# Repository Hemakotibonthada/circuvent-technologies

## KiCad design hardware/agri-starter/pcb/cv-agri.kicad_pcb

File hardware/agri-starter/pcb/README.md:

# Agri Starter PCB - KiCad project + fab checklist

Design source: SCHEMATIC.md (netlist) + BOM.csv. Open cv-agri.kicad_pro in KiCad 8, capture, lay out, export.

## Board spec
- 2-layer FR4, 1.6 mm, HASL lead-free, 2 oz copper on mains.
- >= 8 mm creepage / 6 mm clearance mains-to-LV; isolate each phase-sense input.
- Size target ~ 80 x 60 mm; 4x M3.
- 4 V buck + 1000u bulk at the SIM800L; conformal-coat + IP54 glands for the field.

## Pre-fab (DFM) checklist
- [ ] ERC/DRC clean at fab rules; mains clearances as keepout
- [ ] Contactor-coil relay + flyback verified; phase-sense optos isolated
- [ ] SIM800L on its own 4V buck + bulk cap
- [ ] Test points: 5V, 3V3, GND, IO26/34, UART2
- [ ] UART/EN/IO0 pads for the flashing jig; fiducials

## Export for fab / assembly
- [ ] Gerbers + Excellon -> gerbers/; IPC-356 netlist
- [ ] BOM (BOM.csv) + CPL/centroid; PDF assembly + 3D STEP
- [ ] Order boards + stencil

## Bring-up (EVT)
- [ ] Rails before ESP32; flash test firmware over jig
- [ ] Relay drives a test contactor; mains-sense reads phase HIGH/LOW
- [ ] SIM registers; a missed call toggles the pump
- [ ] Dry-run: pump won't start with sense LOW; auto-restarts on return

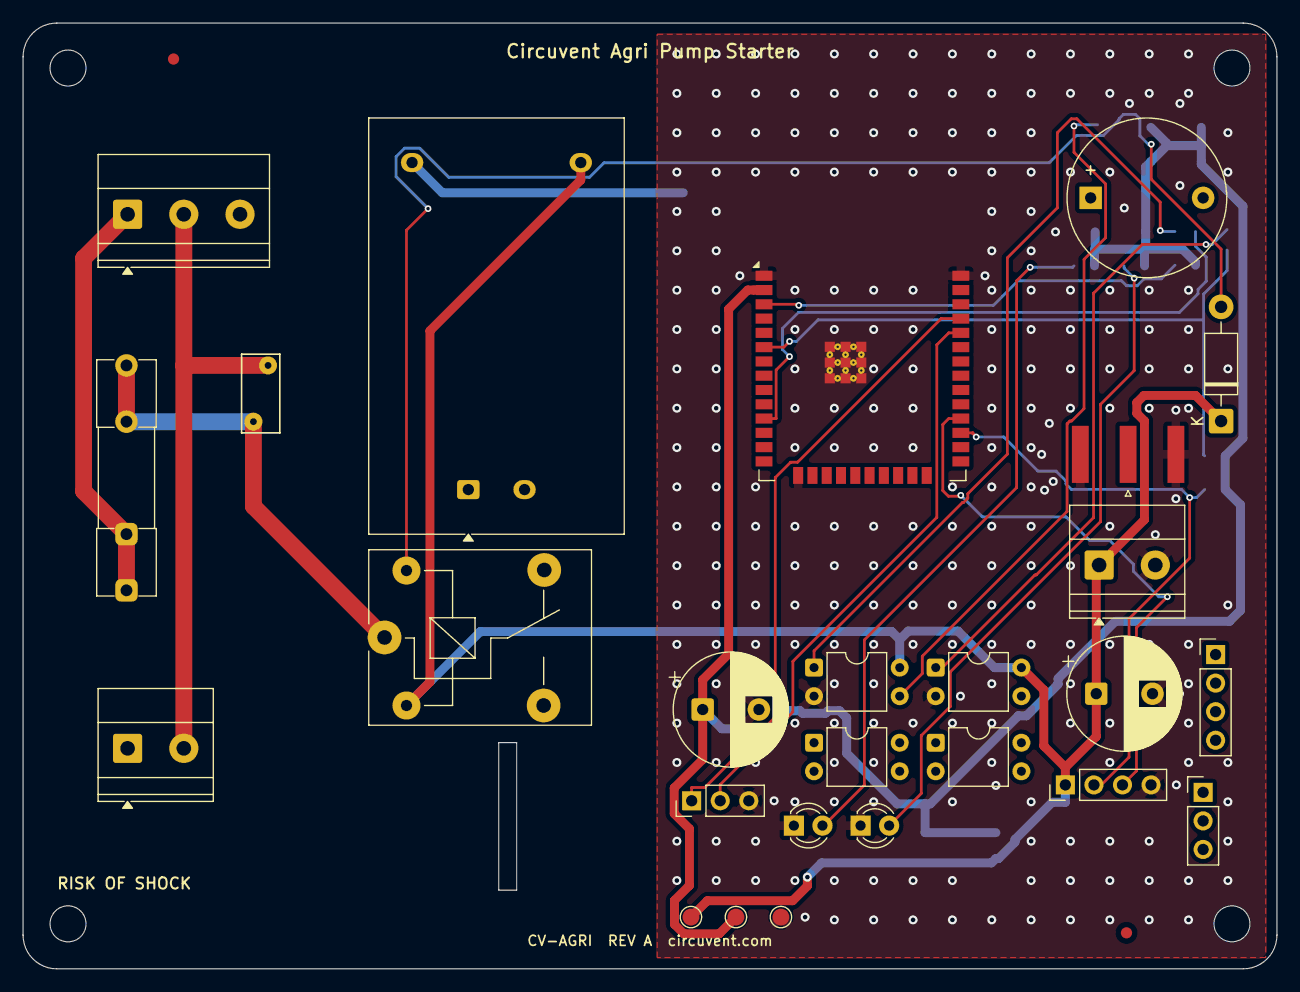
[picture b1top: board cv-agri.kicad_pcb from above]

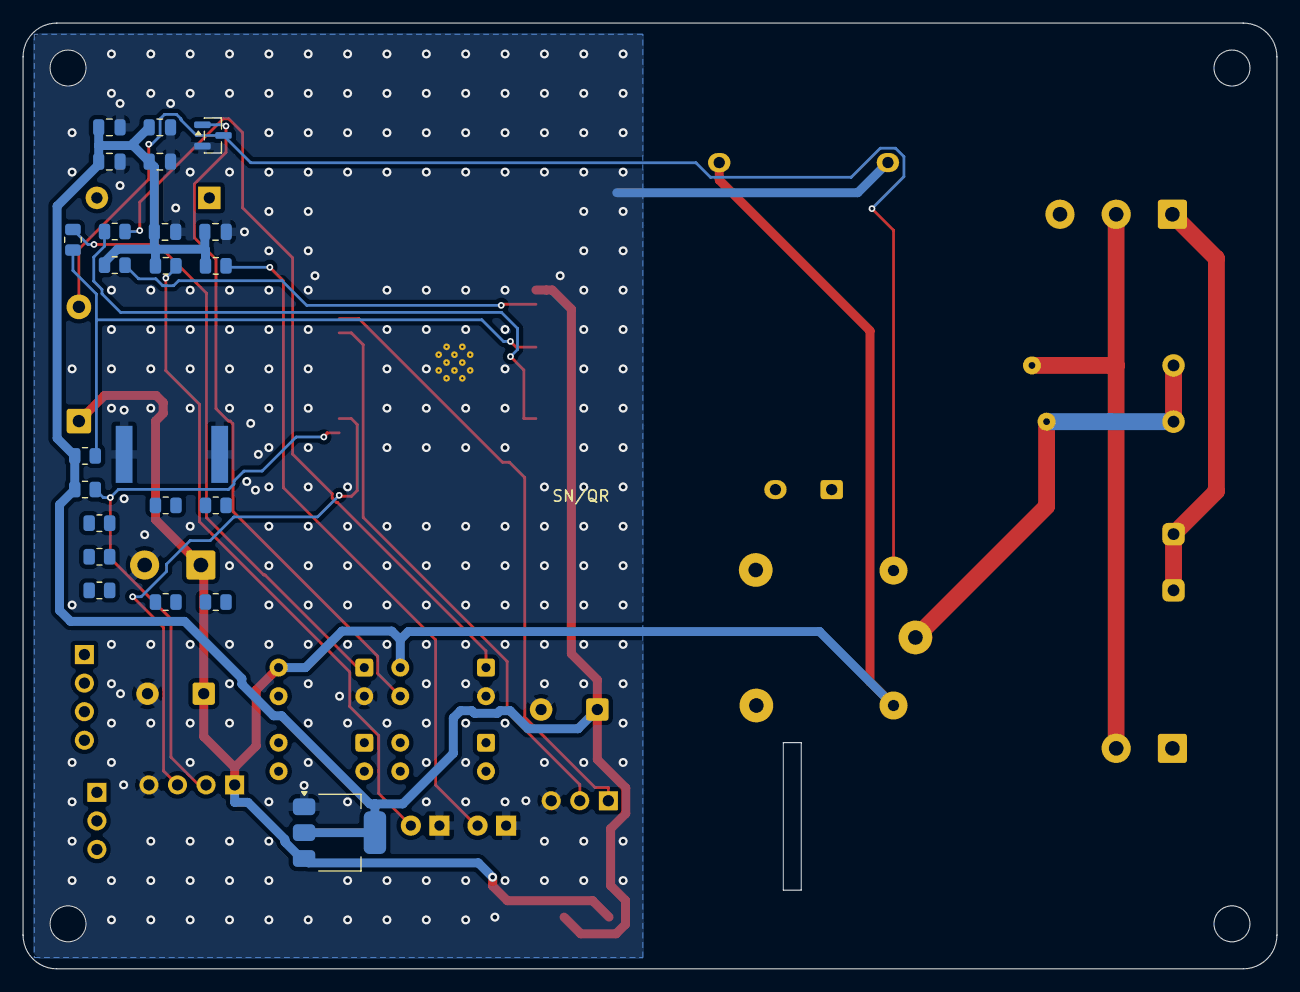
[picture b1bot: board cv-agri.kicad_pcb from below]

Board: 2 copper layers, 111.5 x 84.1 mm, 54 parts (22 on the bottom side), 20 nets.

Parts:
ANT1: GSM antenna (SMA/IPEX); SMA_Amphenol_132289_EdgeMount
C1: 470uF/10V; CP_Radial_D10.0mm_P5.00mm
C2, C3, C4, C5, C6, C7: 100nF/100uF; C_0805_2012Metric
Cs: 1000uF/6.3V; CP_Radial_D10.0mm_P5.00mm
D1: 1N4007; D_DO-41_SOD81_P10.16mm_Horizontal
F1: 1A slow-blow; Fuseholder_Clip-5x20mm_Littelfuse_111_Inline_P20.00x5.00mm_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
FB1: Buzzer 5V; Buzzer_D14mm_H7mm_P10mm
FID1, FID2: Fiducial; Fiducial_1mm_Mask2mm
J1: 2P 5.08mm; TerminalBlock_Phoenix_MKDS-1,5-3_1x03_P5.00mm_Horizontal
J2: 2P 5.08mm; TerminalBlock_Phoenix_MKDS-1,5-2_1x02_P5.00mm_Horizontal
J3: 4P 5.08mm; TerminalBlock_Phoenix_MKDS-1,5-2_1x02_P5.00mm_Horizontal
JP: 3P 2.54mm; PinHeader_1x03_P2.54mm_Vertical
K1: SRD-05VDC-SL-C; Relay_SPDT_SANYOU_SRD_Series_Form_C
LED0, LED1: 3mm; LED_D3.0mm
M1: SIM800L; PinHeader_1x04_P2.54mm_Vertical
MH1, MH2, MH3, MH4: MountingHole; MountingHole_3.2mm_M3
PC1: PC817; DIP-4_W7.62mm
PC2, PC3, PC4: PC814 (AC input); DIP-4_W7.62mm
PS1: HLK-PM01 (5V 3W); Converter_ACDC_Hi-Link_HLK-PMxx
Q1: S8050; SOT-23
R1, R2, R3, R4, R5, R6, R7, R8, R9, R10, R11, R12, R13, R14: 10k/1k/330 + opto R; R_0805_2012Metric
RV1: 7D471K; RV_Disc_D7mm_W3.4mm_P5mm
SIM1: Micro-SIM holder; PinHeader_1x03_P2.54mm_Vertical
TP1: +5V; TestPoint_Pad_D1.5mm
TP2: +3V3; TestPoint_Pad_D1.5mm
TP3: GND; TestPoint_Pad_D1.5mm
U1: ESP32-WROOM-32E (4MB); ESP32-WROOM-32E
U2: AMS1117-3.3; SOT-223-3_TabPin2
U3: MP1584 buck (4V); PinHeader_1x04_P2.54mm_Vertical

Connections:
+3V3: C2.1, C3.1, C4.1, C5.1, C6.1, C7.1, Cs.1, R3.1, R4.1, R5.1, R6.1, R7.1, TP2.1, U1.2, U2.2
+5V: C1.1, D1.1, J3.1, K1.2, M1.1, PC1.4, PC2.4, PS1.4, TP1.1, U2.3
AC_L: F1.1, J1.1
AC_L_FUSED: F1.2, K1.1, PS1.1, RV1.1
AC_N: J1.2, J2.2, PS1.2, RV1.2
EN: R3.2, U1.3
GND: ANT1.2, C1.2, C2.2, C3.2, C4.2, C5.2, C6.2, C7.2, Cs.2, J3.2, JP.3, LED0.1, LED1.1, M1.4, PC1.2, PC2.2, PS1.3, Q1.2, TP3.1, U1.1, U1.15, U1.38, U1.39, U2.1
LED0_A: LED0.2, R4.2
LED1_A: LED1.2, R5.2
MAINS_SENSE: R2.1, R6.2, U1.6
MAINS_SENSE_OPT: PC2.1, R2.2
PUMP_RELAY: R1.1, U1.11
PUMP_RELAY_COIL: D1.2, K1.5, Q1.3
PUMP_RELAY_DRV: PC1.3, Q1.1
PUMP_RELAY_OPT: PC1.1, R1.2
PUMP_RELAY_SW: J2.1, K1.3
SIM_RX: M1.2, R7.2, U1.27
SIM_TX: M1.3, U1.28
UART_RX: JP.2, U1.34
UART_TX: JP.1, U1.35

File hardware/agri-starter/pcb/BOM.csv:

Ref,Qty,Value/Part,Package,Description,Notes
U1,1,ESP32-WROOM-32E (4MB),SMD module,Wi-Fi/BLE MCU module,Main controller
PS1,1,HLK-PM01 (5V 3W),SIP,230VAC -> 5VDC isolated PSU,From one phase
U2,1,AMS1117-3.3,SOT-223,5V -> 3.3V LDO,MCU rail
U3,1,MP1584 buck (4V),module/SMD,5V -> ~4V for SIM800L,2 A capable
M1,1,SIM800L,module,2G GSM (missed call + SMS),
PC1,1,PC817,DIP-4,Opto-isolator,Relay drive
PC2-PC4,3,PC814 (AC input),DIP-4,Phase-present optos,Up to 3 phases
Q1,1,S8050,SOT-23,NPN relay driver,
D1,1,1N4007,DO-41,Flyback diode,Relay coil
K1,1,SRD-05VDC-SL-C,THT relay,5V SPDT 10A,Contactor coil switch
RV1,1,7D471K,disc,MOV 470V,Mains surge clamp
F1,1,1A slow-blow,5x20 holder,Mains fuse,
SIM1,1,Micro-SIM holder,THT,SIM card cage,
ANT1,1,GSM antenna (SMA/IPEX),-,Cellular antenna,
FB1,1,Buzzer 5V,THT,Status/alert buzzer,
C1,1,470uF/10V,electrolytic,5V bulk,
Cs,1,1000uF/6.3V,electrolytic,SIM800L bulk,2 A bursts
LED0-LED1,2,3mm,THT,Power + pump status,
J1,1,2P 5.08mm,terminal,Mains L/N in,
J2,1,2P 5.08mm,terminal,Contactor coil A1/A2,
J3,1,4P 5.08mm,terminal,Phase-sense in (up to 3),
JP,1,3P 2.54mm,header,UART (TX/RX/GND),Factory flashing
R1-R14,14,10k/1k/330 + opto R,0805,Pull/base/LED/sense,
C2-C7,6,100nF/100uF,0805/elec,Decoupling + rails,
PCB,1,2-layer FR4 1.6mm,-,Main board,>=8mm mains-LV creepage; conformal coat
ENC,1,ABS/PC box (IP54),-,Industrial housing,Wall mount + glands

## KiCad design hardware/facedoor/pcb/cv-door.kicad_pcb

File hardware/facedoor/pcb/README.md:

# FaceDoor PCB - KiCad project + fab checklist

Design source: SCHEMATIC.md (netlist) + BOM.csv. Open cv-door.kicad_pro in KiCad, capture, lay out, export.

## Board spec
- 2-layer FR4, 1.6 mm, HASL lead-free, 2 oz copper on mains.
- >= 8 mm creepage / 6 mm clearance mains-to-LV; isolation slots.
- Size target ~ 70 x 55 mm (door-frame enclosure); 4x M3.
- Strike loop carries the highest current: wide traces + thermal relief.

## Pre-fab (DFM) checklist
- [ ] ERC/DRC clean at fab rules; mains clearances as keepout
- [ ] Fail-secure verified: relay de-energised == bolt engaged
- [ ] D2 freewheel fitted across the strike terminals
- [ ] External 10k pull-up on IO39 (input-only, no internal pull-up)
- [ ] Test points: 12V, 5V, 3V3, GND, IO13, keypad rows/cols
- [ ] UART/EN/IO0 pads for the flashing jig; fiducials

## Export for fab / assembly
- [ ] Gerbers + Excellon -> gerbers/; IPC-356 netlist
- [ ] BOM (BOM.csv) + CPL/centroid; PDF assembly + 3D STEP
- [ ] Order boards + stencil

## Bring-up (EVT)
- [ ] Rails before ESP32; flash test firmware over jig
- [ ] Boots locked; re-locks after the configured delay
- [ ] All 16 keypad positions decode; fingerprint enrol + match
- [ ] Bell button raises an event; hub captures the snapshot
- [ ] Power-fail during unlock leaves the door secured

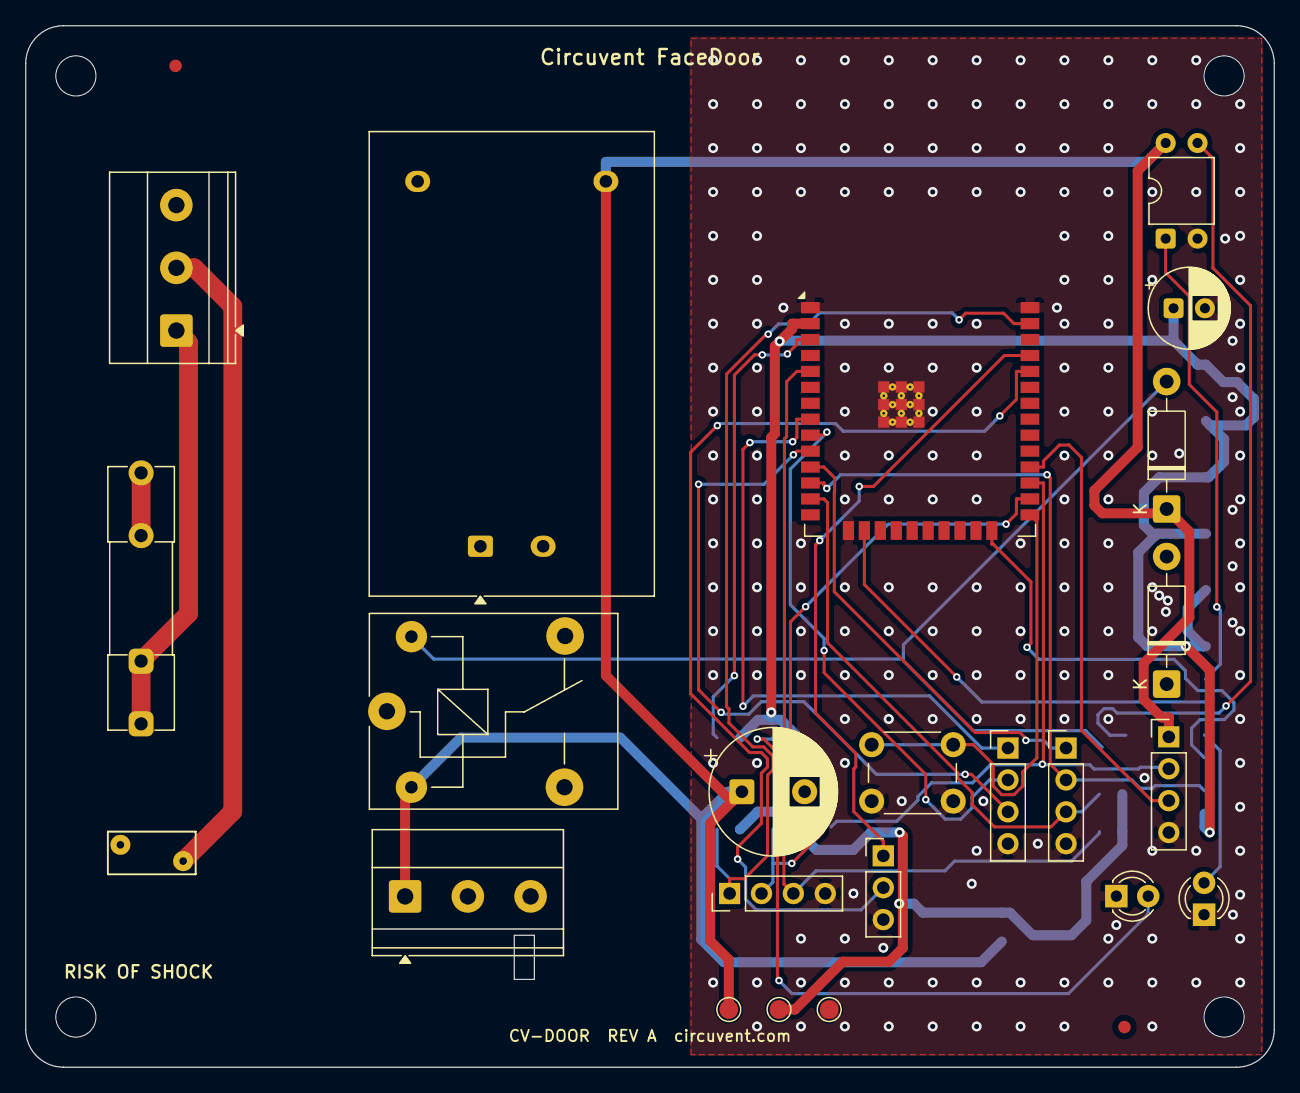
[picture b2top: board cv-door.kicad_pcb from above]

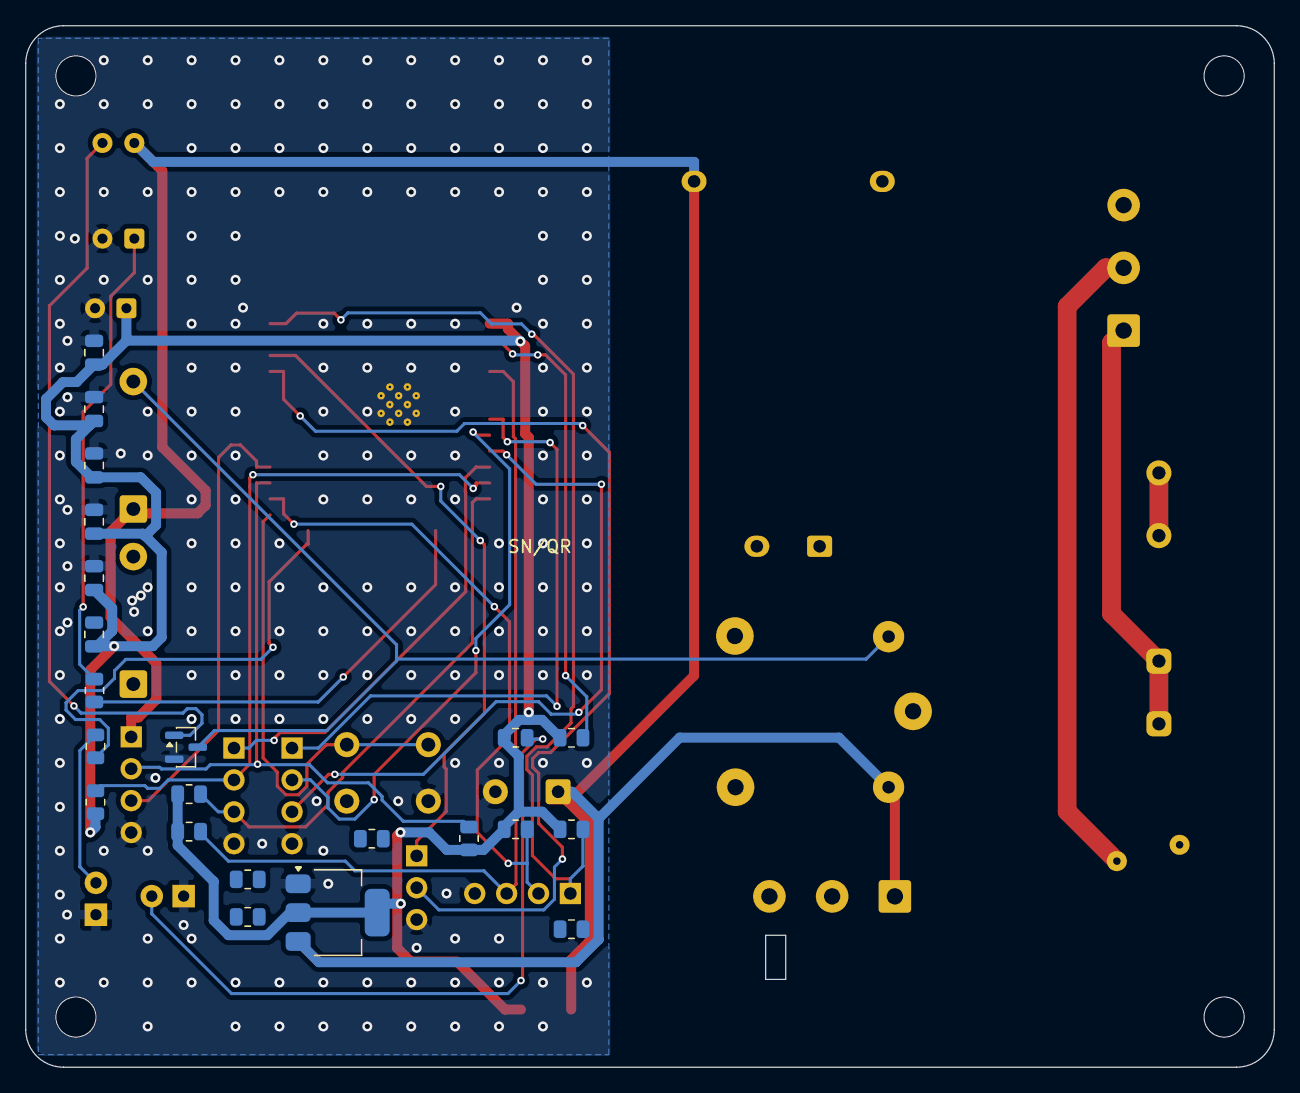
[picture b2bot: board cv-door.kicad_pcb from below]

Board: 2 copper layers, 99.5 x 83.0 mm, 51 parts (22 on the bottom side), 29 nets.

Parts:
C1: 470uF/10V; CP_Radial_D10.0mm_P5.00mm
C2: 100uF/6.3V; CP_Radial_D6.3mm_P2.50mm
C3, C4, C5, C6, C7, C8: 100nF; C_0805_2012Metric
D1, D2: 1N4007; D_DO-41_SOD81_P10.16mm_Horizontal
F1: 1A slow-blow; Fuseholder_Clip-5x20mm_Littelfuse_111_Inline_P20.00x5.00mm_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
FID1, FID2: Fiducial; Fiducial_1mm_Mask2mm
J1: 2P 5.08mm; TerminalBlock_Phoenix_MKDS-1,5-3_1x03_P5.00mm_Horizontal
J2: 3P 5.08mm; TerminalBlock_Phoenix_MKDS-1,5-3_1x03_P5.00mm_Horizontal
J3, J4, J5, J6: 4P 2.54mm; PinHeader_1x04_P2.54mm_Vertical
JP: 3P 2.54mm; PinHeader_1x03_P2.54mm_Vertical
K1: SRD-05VDC-SL-C; Relay_SPDT_SANYOU_SRD_Series_Form_C
LED0: Green 3mm; LED_D3.0mm
LED1: Red 3mm; LED_D3.0mm
MH1, MH2, MH3, MH4: MountingHole; MountingHole_3.2mm_M3
PS1: HLK-PM12 (12V 3W); Converter_ACDC_Hi-Link_HLK-PMxx
Q1: S8050; SOT-23
R1, R2, R3, R4, R5, R6, R7, R8, R9, R10, R11, R12, R13, R14: 10k/1k/330; R_0805_2012Metric
RV1: 7D471K; RV_Disc_D7mm_W3.4mm_P5mm
SW1: 6mm tactile; SW_PUSH_6mm_H5mm
TP1: +5V; TestPoint_Pad_D1.5mm
TP2: +3V3; TestPoint_Pad_D1.5mm
TP3: GND; TestPoint_Pad_D1.5mm
U1: ESP32-WROOM-32E (4MB); ESP32-WROOM-32E
U2: AMS1117-3.3; SOT-223-3_TabPin2
U3: PC817; DIP-4_W7.62mm

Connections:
+3V3: C2.1, C3.1, C4.1, C5.1, C6.1, C7.1, C8.1, R3.1, R4.1, R5.1, R6.1, R7.1, R8.1, R9.1, R10.1, TP2.1, U1.2, U2.2
+5V: C1.1, D1.1, J2.1, J3.1, K1.2, PS1.4, TP1.1, U2.3, U3.4
AC_L: F1.1, J1.1
AC_L_FUSED: F1.2, K1.1, PS1.1, RV1.1
AC_N: J1.2, J2.3, PS1.2, RV1.2
BELL_BTN: J6.3, R10.2, U1.5
BTN_PIN: SW1.1, U1.25
EN: R3.2, U1.3
FP_RX: J3.2, R9.2, U1.27
FP_TX: J3.3, U1.28
GND: C1.2, C2.2, C3.2, C4.2, C5.2, C6.2, C7.2, C8.2, J3.4, J4.4, J5.4, J6.4, JP.3, LED0.1, LED1.1, PS1.3, Q1.2, SW1.2, TP3.1, U1.1, U1.15, U1.38, U1.39, U2.1, U3.2
KP_COL1: J5.2, R5.2, U1.12
KP_COL2: J5.3, R6.2, U1.13
KP_COL3: J6.1, R7.2, U1.37
KP_COL4: J6.2, R8.2, U1.26
KP_ROW1: J4.1, U1.8
KP_ROW2: J4.2, U1.9
KP_ROW3: J4.3, U1.10
KP_ROW4: J5.1, U1.11
LED0_A: LED0.2, R4.2
LED_PIN: R2.1, U1.24
LED_PIN_A: LED1.2, R2.2
LOCK_RELAY: R1.1, U1.16
LOCK_RELAY_COIL: D1.2, K1.5, Q1.3
LOCK_RELAY_DRV: Q1.1, U3.3
LOCK_RELAY_OPT: R1.2, U3.1
LOCK_RELAY_SW: J2.2, K1.3
UART_RX: JP.2, U1.34
UART_TX: JP.1, U1.35

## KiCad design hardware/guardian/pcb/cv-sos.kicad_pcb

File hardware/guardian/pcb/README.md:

# Guardian SOS PCB - KiCad project + fab checklist

Design source: SCHEMATIC.md (netlist) + BOM.csv. Open cv-sos.kicad_pro in KiCad 8, capture, lay out, export.

## Board spec
- 2-layer FR4, 1.6 mm, HASL lead-free.
- Low voltage / battery; RF keep-outs under both antennas.
- Size target ~ 60 x 40 mm (pendant); battery clips + 1x M2.
- 1000u bulk right at the SIM800L VCC; SMA/IPEX for GSM + active GPS antenna.

## Pre-fab (DFM) checklist
- [ ] ERC/DRC clean; antenna keep-outs + ground relief
- [ ] SIM800L powered from BAT + bulk cap (not the LDO)
- [ ] SIM footprint + card cage; USB-C charge path
- [ ] Test points: BAT, 3V3, GND, IO0/25/34, UART1/2
- [ ] UART/EN/IO0 pads for the flashing jig; fiducials

## Export for fab / assembly
- [ ] Gerbers + Excellon -> gerbers/; IPC-356 netlist
- [ ] BOM (BOM.csv) + CPL/centroid; PDF assembly + 3D STEP
- [ ] Order boards + stencil

## Bring-up (EVT)
- [ ] Charge cell; rails up; flash test firmware over jig
- [ ] SIM800L registers on the network; SMS + call succeed
- [ ] GPS gets a fix outdoors; battery % reads sane
- [ ] SOS button -> SMS(location) + call + cloud alert; buzzer confirms

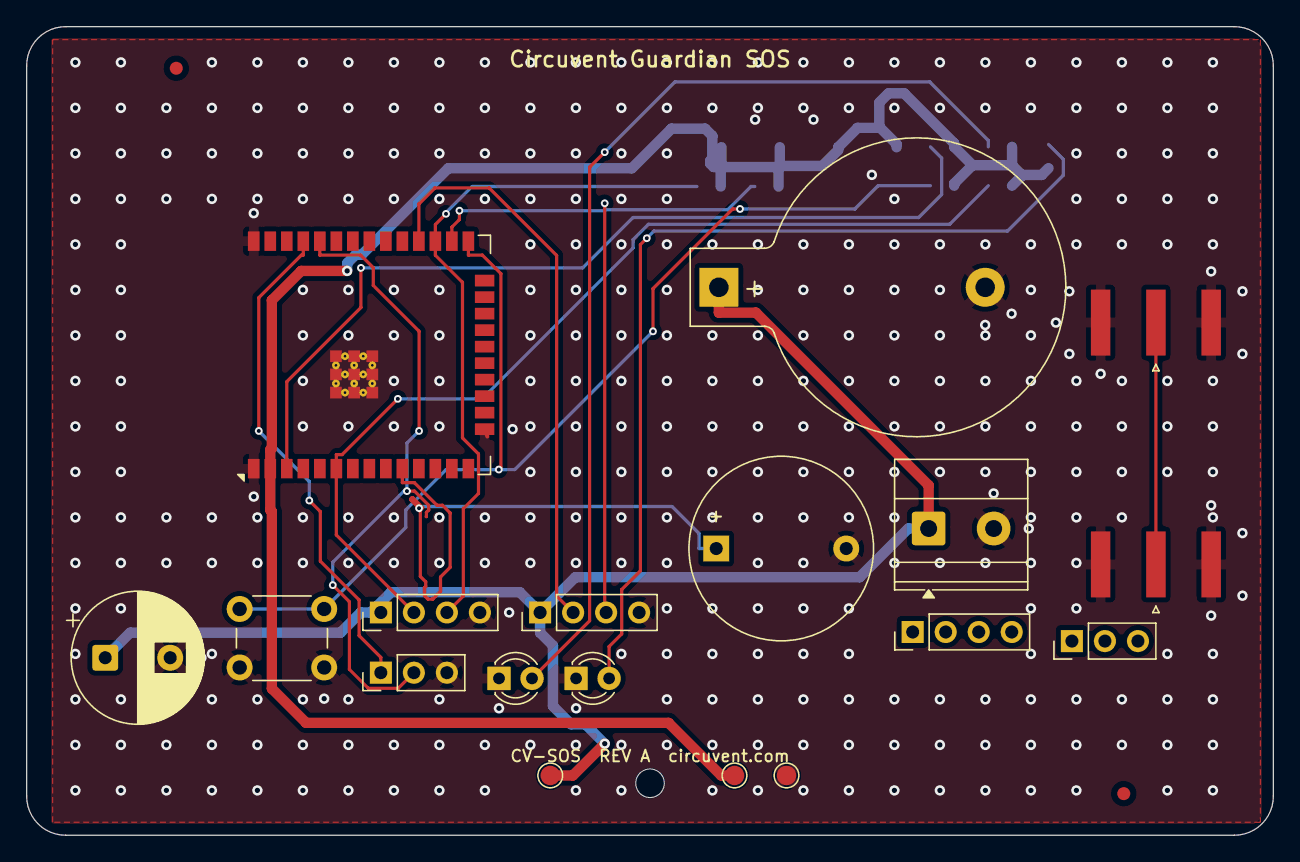
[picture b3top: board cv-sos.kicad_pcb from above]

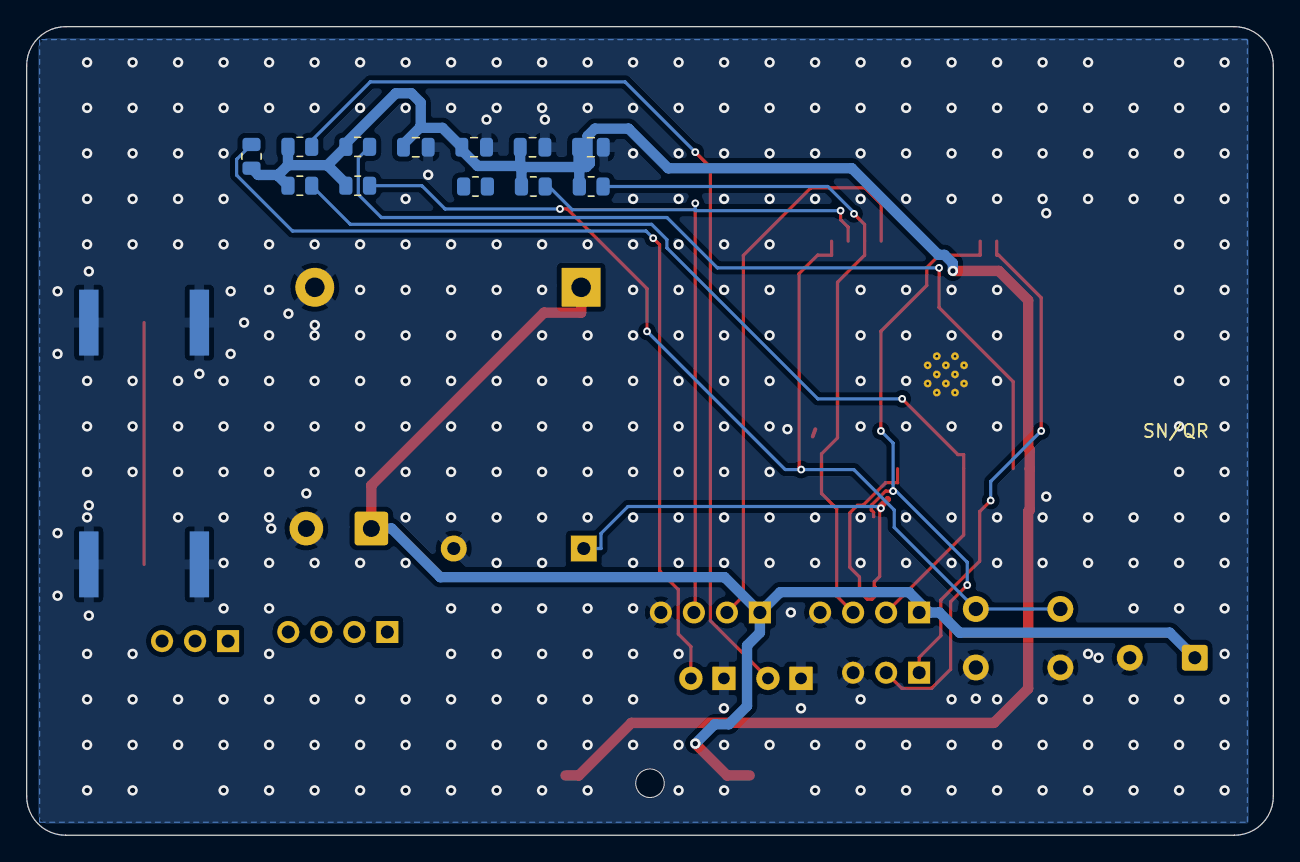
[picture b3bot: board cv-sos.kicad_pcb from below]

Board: 2 copper layers, 95.9 x 62.2 mm, 33 parts (12 on the bottom side), 15 nets.

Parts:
ANT1: GSM antenna (SMA/IPEX); SMA_Amphenol_132289_EdgeMount
ANT2: GPS active antenna; SMA_Amphenol_132289_EdgeMount
BT1: 18650 Li-ion + holder; BatteryHolder_Keystone_103_1x20mm
C1: 1000uF/6.3V; CP_Radial_D10.0mm_P5.00mm
C2, C3, C4, C5: 100nF/100uF; C_0805_2012Metric
FB1: Magnetic buzzer 5V; Buzzer_D14mm_H7mm_P10mm
FID1, FID2: Fiducial; Fiducial_1mm_Mask2mm
J1: USB-C 16P; TerminalBlock_Phoenix_MKDS-1,5-2_1x02_P5.00mm_Horizontal
JP: 3P 2.54mm; PinHeader_1x03_P2.54mm_Vertical
LED0, LED1: 3mm; LED_D3.0mm
M1: SIM800L; PinHeader_1x04_P2.54mm_Vertical
M2: NEO-6M / L80; PinHeader_1x04_P2.54mm_Vertical
MH1: MountingHole; MountingHole_2.2mm_M2
R1, R2, R3, R4, R5, R6, R7, R8: 100k/10k/330; R_0805_2012Metric
SIM1: Micro-SIM holder; PinHeader_1x03_P2.54mm_Vertical
SW1: Tactile 6mm (guarded); SW_PUSH_6mm_H5mm
TP1: +5V; TestPoint_Pad_D1.5mm
TP2: +3V3; TestPoint_Pad_D1.5mm
TP3: GND; TestPoint_Pad_D1.5mm
U1: ESP32-WROOM-32E (4MB); ESP32-WROOM-32E
U3: TP4056 + DW01/8205; PinHeader_1x04_P2.54mm_Vertical

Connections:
+3V3: C2.1, C3.1, C4.1, C5.1, R1.1, R2.1, R3.1, R4.1, R5.1, R6.1, R7.1, TP2.1, U1.2
+5V: BT1.1, C1.1, J1.1, M1.1, M2.1, TP1.1
ANT: ANT1.1, ANT2.1
BATT_ADC: M1.2, R5.2, U1.6
BUZZER: FB1.1, U1.10
EN: R1.2, U1.3
GND: ANT1.2, ANT2.2, BT1.2, C1.2, C2.2, C3.2, C4.2, C5.2, FB1.2, J1.2, JP.3, LED0.1, LED1.1, M1.4, M2.4, SW1.2, TP3.1, U1.1, U1.15, U1.38, U1.39
GPS_RX: M2.3, R7.2, U1.26
LED0_A: LED0.2, R2.2
LED1_A: LED1.2, R3.2
SIM_RX: M1.3, R6.2, U1.27
SIM_TX: M2.2, U1.28
SOS_BTN: R4.2, SW1.1, U1.25
UART_RX: JP.2, U1.34
UART_TX: JP.1, U1.35

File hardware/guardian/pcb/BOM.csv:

Ref,Qty,Value/Part,Package,Description,Notes
U1,1,ESP32-WROOM-32E (4MB),SMD module,Wi-Fi/BLE MCU module,Main controller
M1,1,SIM800L,module,2G GSM (SMS + voice),From BAT + bulk
M2,1,NEO-6M / L80,module,GPS receiver,Active antenna
U3,1,TP4056 + DW01/8205,module,Li-ion charge + protection,USB-C
BT1,1,18650 Li-ion + holder,cell,Battery,Protected
FB1,1,Magnetic buzzer 5V,THT,Confirmation buzzer,
SW1,1,Tactile 6mm (guarded),THT,SOS button,Also BOOT
J1,1,USB-C 16P,SMD,Charge in,
ANT1,1,GSM antenna (SMA/IPEX),-,Cellular antenna,
ANT2,1,GPS active antenna,-,GPS antenna,
SIM1,1,Micro-SIM holder,THT,SIM card cage,
C1,1,1000uF/6.3V,electrolytic,SIM800L bulk,2 A bursts
LED0-LED1,2,3mm,THT,Power + status,
R1-R8,8,100k/10k/330,0805,Divider/pull/LED,
C2-C5,4,100nF/100uF,0805/elec,Decoupling + rails,
JP,1,3P 2.54mm,header,UART (TX/RX/GND),Factory flashing
PCB,1,2-layer FR4 1.6mm,-,Main board,Antenna keep-outs
ENC,1,ABS pendant (IP54),-,Handheld housing,Lanyard loop + SOS cap

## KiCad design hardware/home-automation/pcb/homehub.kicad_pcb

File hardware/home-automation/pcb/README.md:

# Home Automation Hub PCB - KiCad project + fab checklist

Design source: `SCHEMATIC.md` (netlist) + `BOM.csv`. Open `homehub.kicad_pro`
in **KiCad 8**, capture, lay out, export.

## Board spec
- 2-layer FR4, 1.6 mm, HASL lead-free, 2 oz copper on mains.
- >= 8 mm creepage / 6 mm clearance mains-to-LV; isolation slots.
- Size target ~ 90 x 65 mm; 4x M3 mounts. Relay pads wide + thermal relief.

## Pre-fab (DFM) checklist
- [ ] ERC/DRC clean at fab rules; mains clearances as keepout
- [ ] Fuse + MOV at entry; single L-bus to 4 relay COMs
- [ ] Per-channel derating printed on silk; total load <= fuse/PSU/copper limit
- [ ] Test points: 5V, 3V3, GND, IO26/27/32/33 (relays), buttons
- [ ] UART/EN/IO0 pads for the flashing jig; fiducials; panelize

## Export for fab / assembly
- [ ] Gerbers + Excellon -> `gerbers/`; IPC-356 netlist
- [ ] BOM (`BOM.csv`) + CPL/centroid; PDF assembly + 3D STEP
- [ ] Order boards + stencil

## Bring-up (EVT)
- [ ] Rails before ESP32; flash test firmware over jig
- [ ] Each relay clicks + switches its output; buttons toggle locally (offline)
- [ ] Cloud sync self-test; scenes + schedule fire

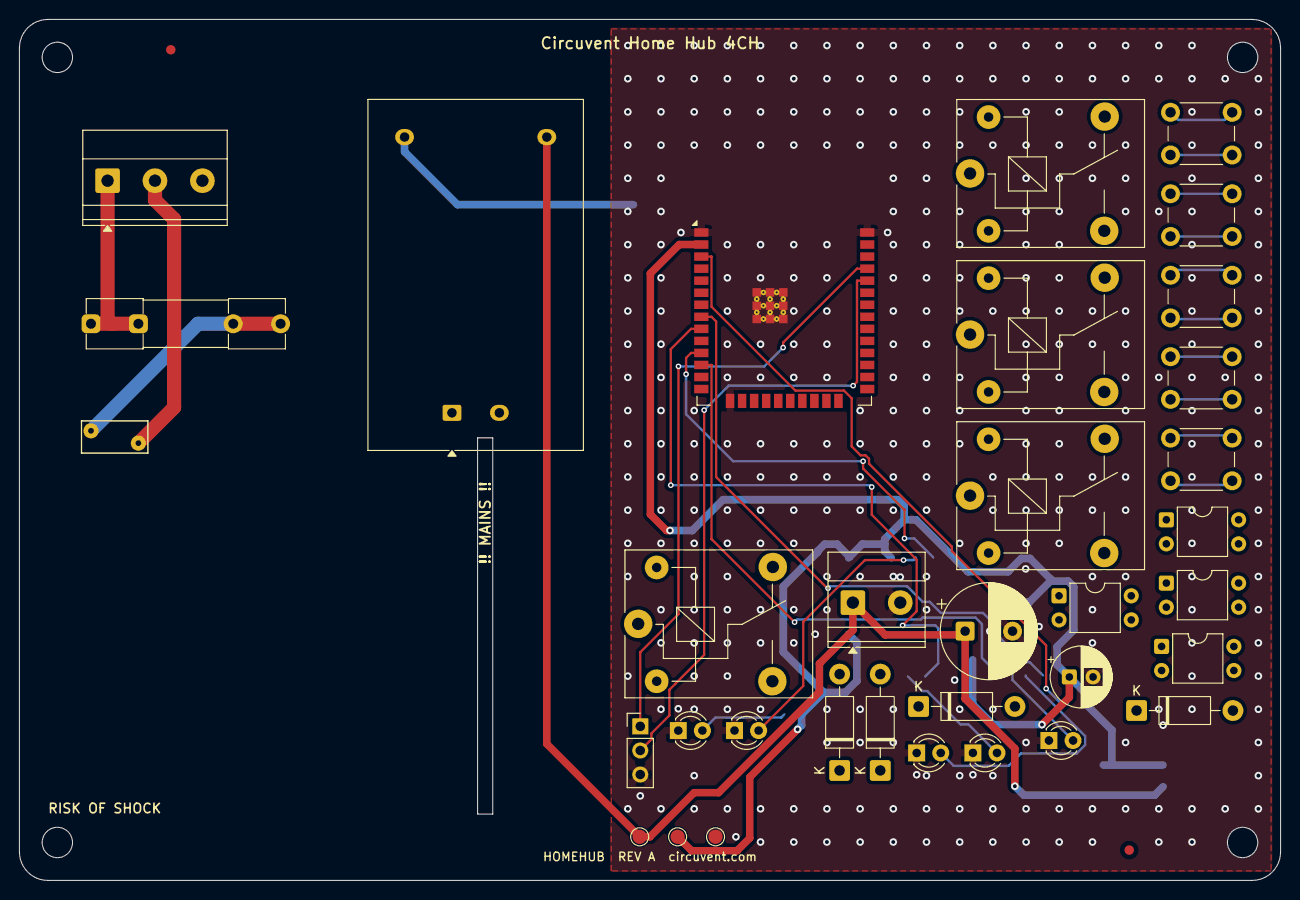
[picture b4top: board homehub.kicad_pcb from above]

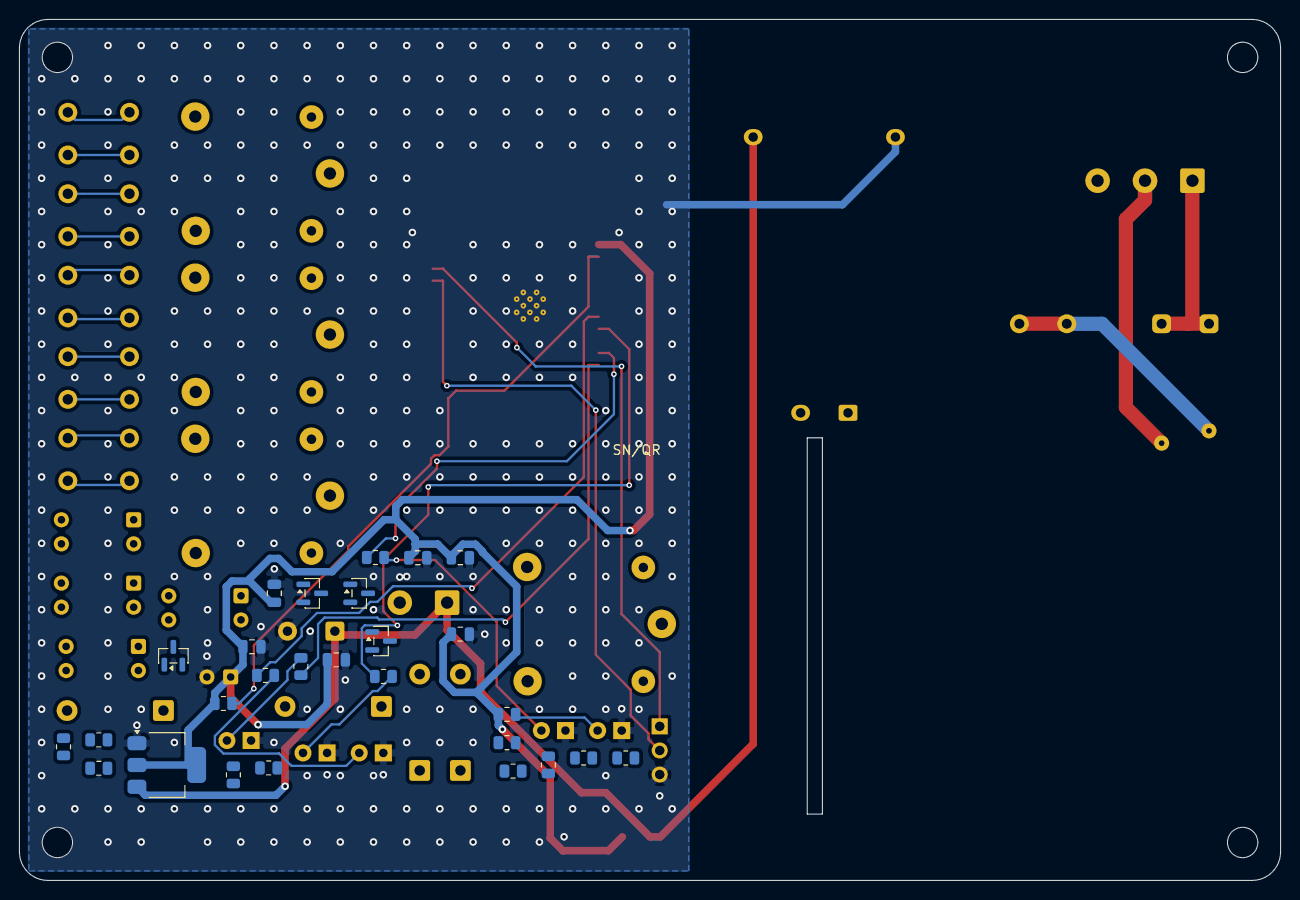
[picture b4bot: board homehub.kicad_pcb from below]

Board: 2 copper layers, 133.0 x 90.8 mm, 67 parts (27 on the bottom side), 18 nets.

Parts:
C1: 1000uF/10V; CP_Radial_D10.0mm_P5.00mm
C2: 100uF/6.3V; CP_Radial_D6.3mm_P2.50mm
C3, C4, C5, C6, C7, C8: 100nF; C_0805_2012Metric
D1, D2, D3, D4: 1N4007; D_DO-41_SOD81_P10.16mm_Horizontal
F1: 6A slow-blow; Fuseholder_Clip-5x20mm_Littelfuse_111_Inline_P20.00x5.00mm_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
FID1, FID2: Fiducial; Fiducial_1mm_Mask2mm
J1: 2P 5.08mm; TerminalBlock_Phoenix_MKDS-1,5-3_1x03_P5.00mm_Horizontal
J2: 5P 5.08mm; TerminalBlock_Phoenix_MKDS-1,5-2_1x02_P5.00mm_Horizontal
JP: 3P 2.54mm; PinHeader_1x03_P2.54mm_Vertical
K1, K2, K3, K4: SRD-05VDC-SL-C; Relay_SPDT_SANYOU_SRD_Series_Form_C
LED0: Green 3mm; LED_D3.0mm
LED1, LED2, LED3, LED4: Blue 3mm; LED_D3.0mm
MH1, MH2, MH3, MH4: MountingHole; MountingHole_3.2mm_M3
PS1: HLK-PM03 (5V 3W); Converter_ACDC_Hi-Link_HLK-PMxx
Q1, Q2, Q3, Q4: S8050; SOT-23
R1, R2, R3, R4, R5, R6, R7, R8, R9, R10, R11, R12, R13, R14, R15, R16: 10k/1k/330; R_0805_2012Metric
RV1: 7D471K; RV_Disc_D7mm_W3.4mm_P5mm
SW1, SW2, SW3, SW4, SW5: Tactile 6mm; SW_PUSH_6mm_H5mm
TP1: +5V; TestPoint_Pad_D1.5mm
TP2: +3V3; TestPoint_Pad_D1.5mm
TP3: GND; TestPoint_Pad_D1.5mm
U1: ESP32-WROOM-32E (4MB); ESP32-WROOM-32E
U2: AMS1117-3.3; SOT-223-3_TabPin2
U3, U4, U5, U6: PC817; DIP-4_W7.62mm

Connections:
0: R1.1, U1.11
0_A: LED1.2, R1.2
1: R2.1, U1.12
1_A: LED2.2, R2.2
2: R3.1, U1.8
2_A: LED3.2, R3.2
3: R4.1, U1.9
3_A: LED4.2, R4.2
+3V3: C2.1, C3.1, C4.1, C5.1, C6.1, C7.1, C8.1, R5.1, R6.1, TP2.1, U1.2, U2.2
+5V: C1.1, J2.1, PS1.4, TP1.1, U2.3
AC_L: F1.1, J1.1
AC_L_FUSED: F1.2, PS1.1, RV1.1
AC_N: J1.2, PS1.2, RV1.2
EN: R5.2, U1.3
GND: C1.2, C2.2, C3.2, C4.2, C5.2, C6.2, C7.2, C8.2, J2.2, JP.3, LED0.1, LED1.1, LED2.1, LED3.1, LED4.1, PS1.3, TP3.1, U1.1, U1.15, U1.38, U1.39, U2.1
LED0_A: LED0.2, R6.2
UART_RX: JP.2, U1.34
UART_TX: JP.1, U1.35

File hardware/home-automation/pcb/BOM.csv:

Ref,Qty,Value/Part,Package,Description,Notes
U1,1,ESP32-WROOM-32E (4MB),SMD module,Wi-Fi/BLE MCU module,Main controller
PS1,1,HLK-PM03 (5V 3W),SIP,230VAC -> 5VDC isolated PSU,Sized for 4 relay coils
U2,1,AMS1117-3.3,SOT-223,5V -> 3.3V LDO,MCU rail
U3-U6,4,PC817,DIP-4,Opto-isolators,One per relay channel
Q1-Q4,4,S8050,SOT-23/TO-92,NPN relay drivers,
D1-D4,4,1N4007,DO-41,Flyback diodes,Across each relay coil
K1-K4,4,SRD-05VDC-SL-C,THT relay,5V SPDT 10A,Switch mains loads (recommend <=6A/ch resistive)
RV1,1,7D471K,disc,MOV 470V,Mains surge clamp
F1,1,6A slow-blow,5x20 holder,Mains fuse,Total board load
SW1-SW4,4,Tactile 6mm,THT,Per-channel manual buttons,
SW5,1,Tactile 6mm,THT,BOOT/config button,Hold for Wi-Fi setup
LED0,1,Green 3mm,THT,Power/online,
LED1-LED4,4,Blue 3mm,THT,Channel status,
J1,1,2P 5.08mm,terminal,Mains input L/N,
J2,1,5P 5.08mm,terminal,4x switched-L out + common N,Loads
JP,1,3P 2.54mm,header,UART (TX/RX/GND),Factory flashing
R1-R16,16,10k/1k/330,0805,Pull-ups/base/LED resistors,
C1,1,1000uF/10V,electrolytic,5V bulk (relay inrush),
C2,1,100uF/6.3V,electrolytic,3.3V rail,
C3-C8,6,100nF,0805,Decoupling,
PCB,1,2-layer FR4 1.6mm,-,Main board,>=8mm mains-LV creepage; 2oz Cu; relay pads wide
ENC,1,ABS enclosure (modular/DIN option),-,Wall box,Light-pipes + button caps

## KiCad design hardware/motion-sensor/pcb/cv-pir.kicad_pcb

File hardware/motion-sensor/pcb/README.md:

# Motion Sensor PCB - KiCad project + fab checklist

Design source: SCHEMATIC.md (netlist) + BOM.csv. Open cv-pir.kicad_pro in KiCad 8, capture, lay out, export.

## Board spec
- 2-layer FR4, 1.6 mm, HASL lead-free.
- Low-voltage only (unless the optional mains relay is populated - then isolate it).
- Size target ~ 45 x 35 mm; 2x M3 / adhesive.
- Reserve a corner keep-out under the PIR dome; battery + charger on the back.

## Pre-fab (DFM) checklist
- [ ] ERC/DRC clean at fab rules
- [ ] PIR OUT level matches 3V3 logic
- [ ] Optional relay section isolated if it switches mains
- [ ] Test points: 5V, 3V3, GND, IO27/2
- [ ] UART/EN/IO0 pads for the flashing jig; fiducials

## Export for fab / assembly
- [ ] Gerbers + Excellon -> gerbers/; IPC-356 netlist
- [ ] BOM (BOM.csv) + CPL/centroid; PDF assembly + 3D STEP
- [ ] Order boards + stencil

## Bring-up (EVT)
- [ ] Rail before ESP32; flash test firmware over jig
- [ ] PIR triggers -> LED + cloud alert; arm/disarm works
- [ ] Battery variant: TP4056 charges; runtime measured
- [ ] Cloud sync self-test; automation fires a light

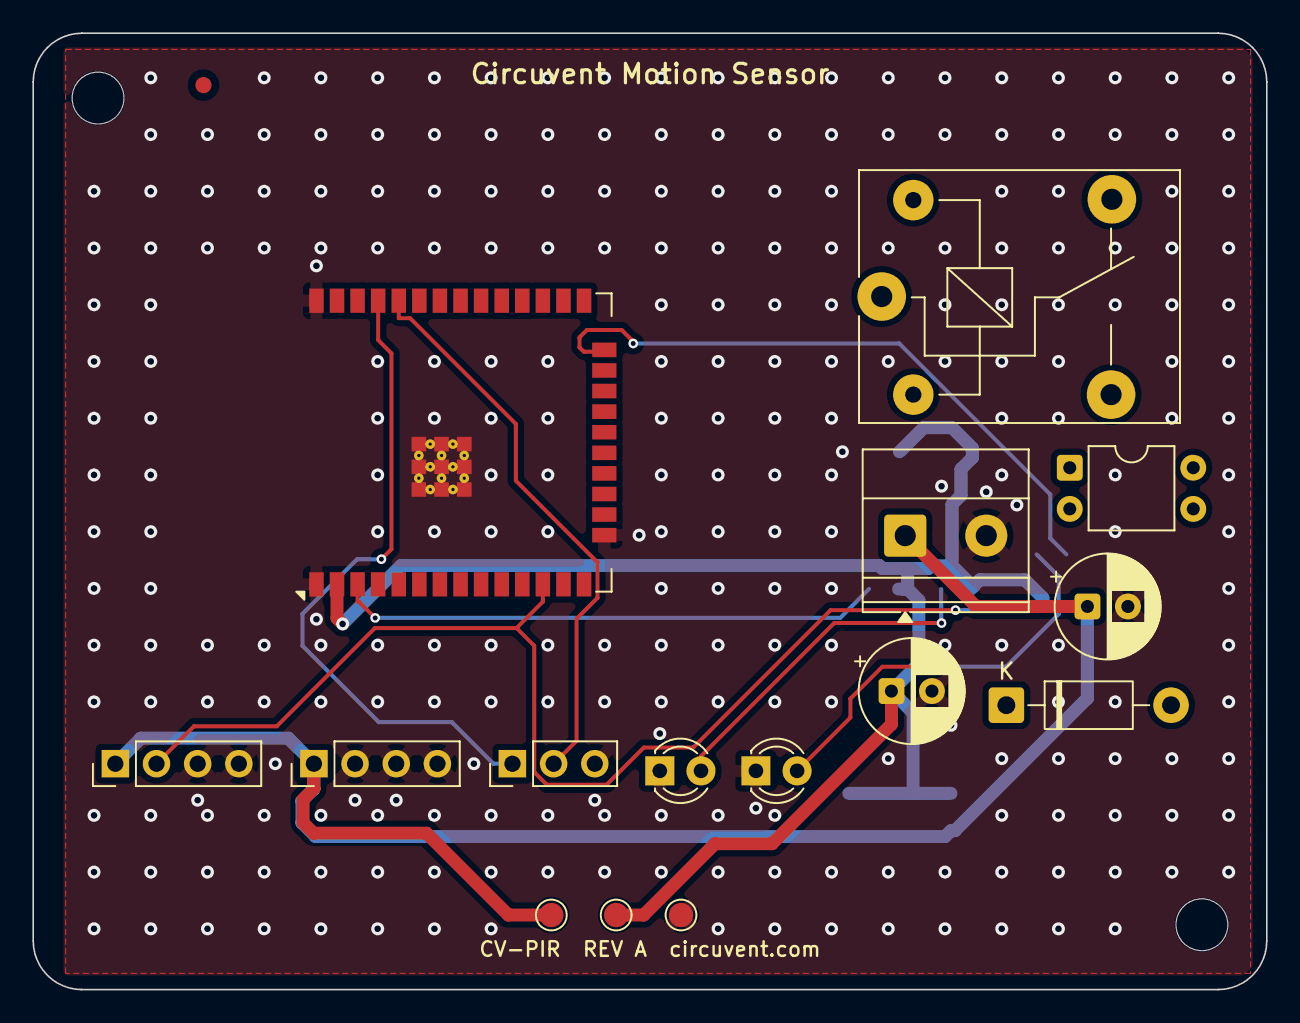
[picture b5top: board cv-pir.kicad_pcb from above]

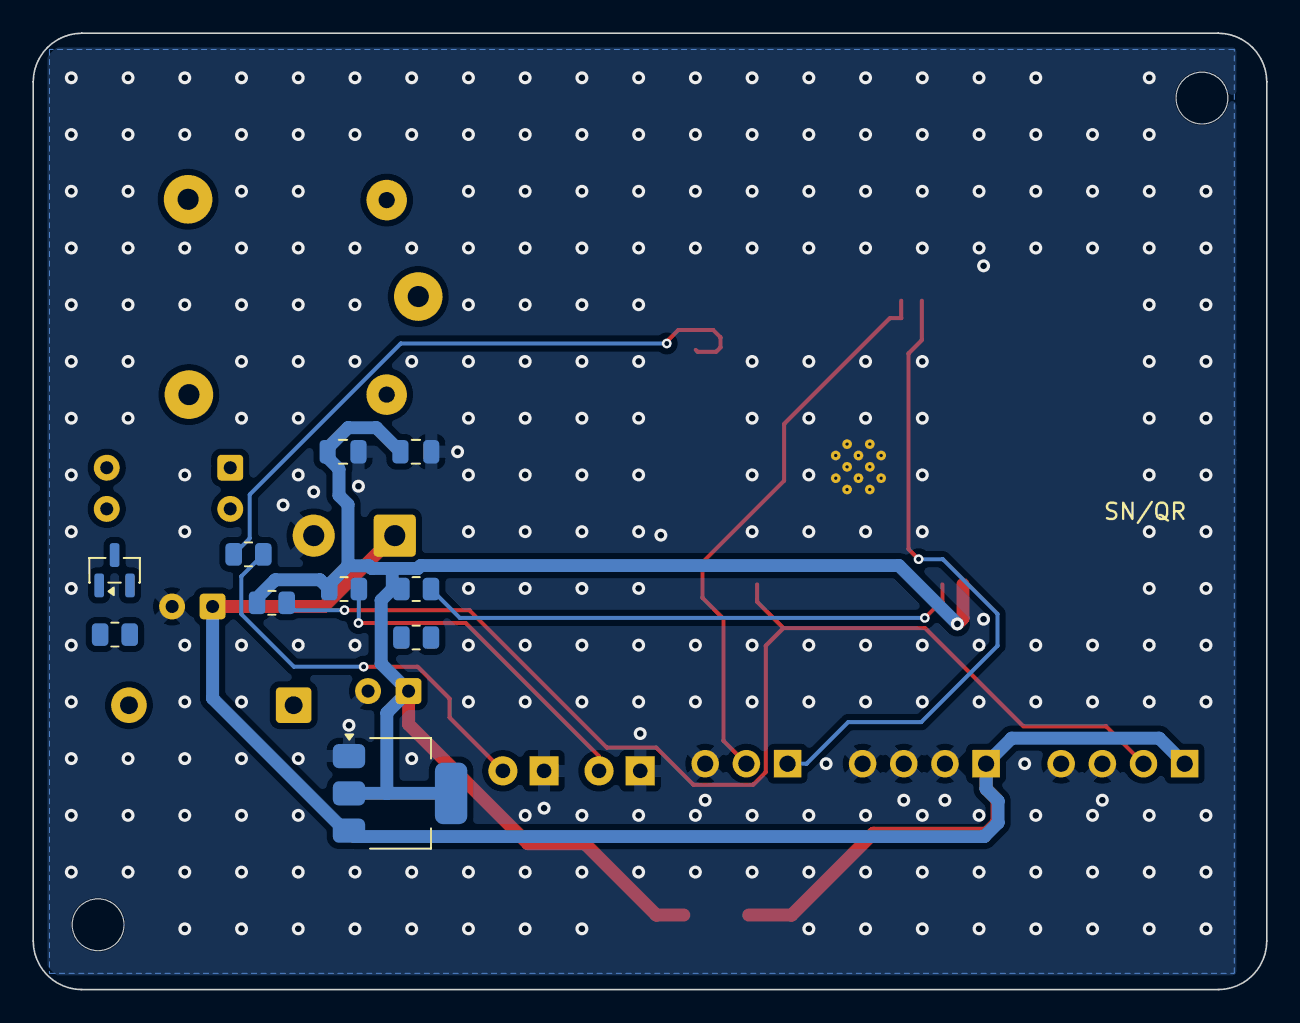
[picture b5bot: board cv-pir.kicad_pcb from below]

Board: 2 copper layers, 76.1 x 59.0 mm, 28 parts (10 on the bottom side), 10 nets.

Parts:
BT1: TP4056 + DW01/8205 + 18650 holder; PinHeader_1x04_P2.54mm_Vertical
C1, C2: 100uF; CP_Radial_D6.3mm_P2.50mm
C3, C4: 100nF; C_0805_2012Metric
D1: 1N4007; D_DO-41_SOD81_P10.16mm_Horizontal
FID1: Fiducial; Fiducial_1mm_Mask2mm
J1: USB-C 16P; TerminalBlock_Phoenix_MKDS-1,5-2_1x02_P5.00mm_Horizontal
JP: 3P 2.54mm; PinHeader_1x03_P2.54mm_Vertical
K1: SRD-05; Relay_SPDT_SANYOU_SRD_Series_Form_C
LED0: Green 3mm; LED_D3.0mm
LED1: Pink 3mm; LED_D3.0mm
M1: HC-SR501 PIR; PinHeader_1x04_P2.54mm_Vertical
MH1, MH2: MountingHole; MountingHole_3.2mm_M3
Q1: S8050; SOT-23
R1, R2, R3, R4, R5, R6: 10k/330; R_0805_2012Metric
TP1: +5V; TestPoint_Pad_D1.5mm
TP2: +3V3; TestPoint_Pad_D1.5mm
TP3: GND; TestPoint_Pad_D1.5mm
U1: ESP32-WROOM-32E (4MB); ESP32-WROOM-32E
U2: AMS1117-3.3; SOT-223-3_TabPin2
U3: PC817; DIP-4_W7.62mm

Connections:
+3V3: C2.1, C3.1, C4.1, R2.1, R3.1, R4.1, TP2.1, U1.2, U2.2
+5V: BT1.1, C1.1, J1.1, M1.1, TP1.1, U2.3
EN: R2.2, U1.3
GND: BT1.2, BT1.3, BT1.4, C1.2, C2.2, C3.2, C4.2, J1.2, JP.3, LED0.1, LED1.1, M1.3, M1.4, TP3.1, U1.1, U1.15, U1.38, U1.39, U2.1
LED0_A: LED0.2, R3.2
LED_PIN: R1.1, U1.24
LED_PIN_A: LED1.2, R1.2
PIR_PIN: M1.2, R4.2, U1.12
UART_RX: JP.2, U1.34
UART_TX: JP.1, U1.35

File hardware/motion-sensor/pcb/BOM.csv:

Ref,Qty,Value/Part,Package,Description,Notes
U1,1,ESP32-WROOM-32E (4MB),SMD module,Wi-Fi/BLE MCU module,Main controller
M1,1,HC-SR501 PIR,module,PIR motion sensor,Dome + lens
U2,1,AMS1117-3.3,SOT-223,5V -> 3.3V LDO,MCU rail
J1,1,USB-C 16P,SMD,5V power in,
LED0,1,Green 3mm,THT,Power/online,
LED1,1,Pink 3mm,THT,Motion / armed,
R1-R6,6,10k/330,0805,Pull/LED resistors,
C1-C2,2,100uF,electrolytic,5V + 3.3V,
C3-C4,2,100nF,0805,Decoupling,
BT1,1,TP4056 + DW01/8205 + 18650 holder,module,Charger + protect + cell,Battery variant only
U3/Q1/K1/D1,1,PC817 + S8050 + SRD-05 + 1N4007,mixed,Optional light relay,Local-light variant only
JP,1,3P 2.54mm,header,UART (TX/RX/GND),Factory flashing
PCB,1,2-layer FR4 1.6mm,-,Main board,PIR keep-out corner
ENC,1,ABS dome/corner (UL94 V-0),-,Sensor housing,Fresnel lens window
